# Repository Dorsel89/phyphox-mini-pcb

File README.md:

# phyphox:mini – PCB

KiCad project for the **phyphox:mini**, a small Bluetooth LE sensor board that
streams its measurements to the [phyphox](https://phyphox.org) app.

The design files were created with **KiCad 10**. Older KiCad versions cannot
open them.

## Hardware

| Part | Function |
|---|---|
| Nordic **nRF52832** (QFN48) | MCU with Bluetooth LE, internal DC/DC converter |
| ST **LSM6DSR** | accelerometer and gyroscope |
| Bosch **BMP580** | air pressure and temperature |
| TI **HDC1080** | relative humidity and temperature |
| Sensirion **STCC4** | CO₂ |
| Renesas/Adesto **AT25FF161A** | 16 Mbit (2 MB) SPI flash for data logging and firmware updates |
| 32 MHz and 32.768 kHz crystals | radio clock and low-power real-time clock |
| PCB antenna | 2.4 GHz, after TI application note SWRA117D |
| LED, test pads | status LED, programming and debugging (SWD) |

- 4-layer board, about 20 × 30 mm
- IMU and flash are connected via SPI; pressure, humidity and CO₂ sensors
  share one I²C bus.

## Files

| Path | Content |
|---|---|
| `Keyfob_2025_nrf52832.kicad_pro` | KiCad project |
| `Keyfob_2025_nrf52832.kicad_sch` | schematic |
| `Keyfob_2025_nrf52832.kicad_pcb` | board layout |
| `lib/` | project symbols (`*.kicad_sym`), footprints (`phyphox-footprints.pretty`) and 3D models (`3d/`) |

The project libraries are referenced relative to the project directory
(`sym-lib-table`, `fp-lib-table`), so the project opens without further setup.

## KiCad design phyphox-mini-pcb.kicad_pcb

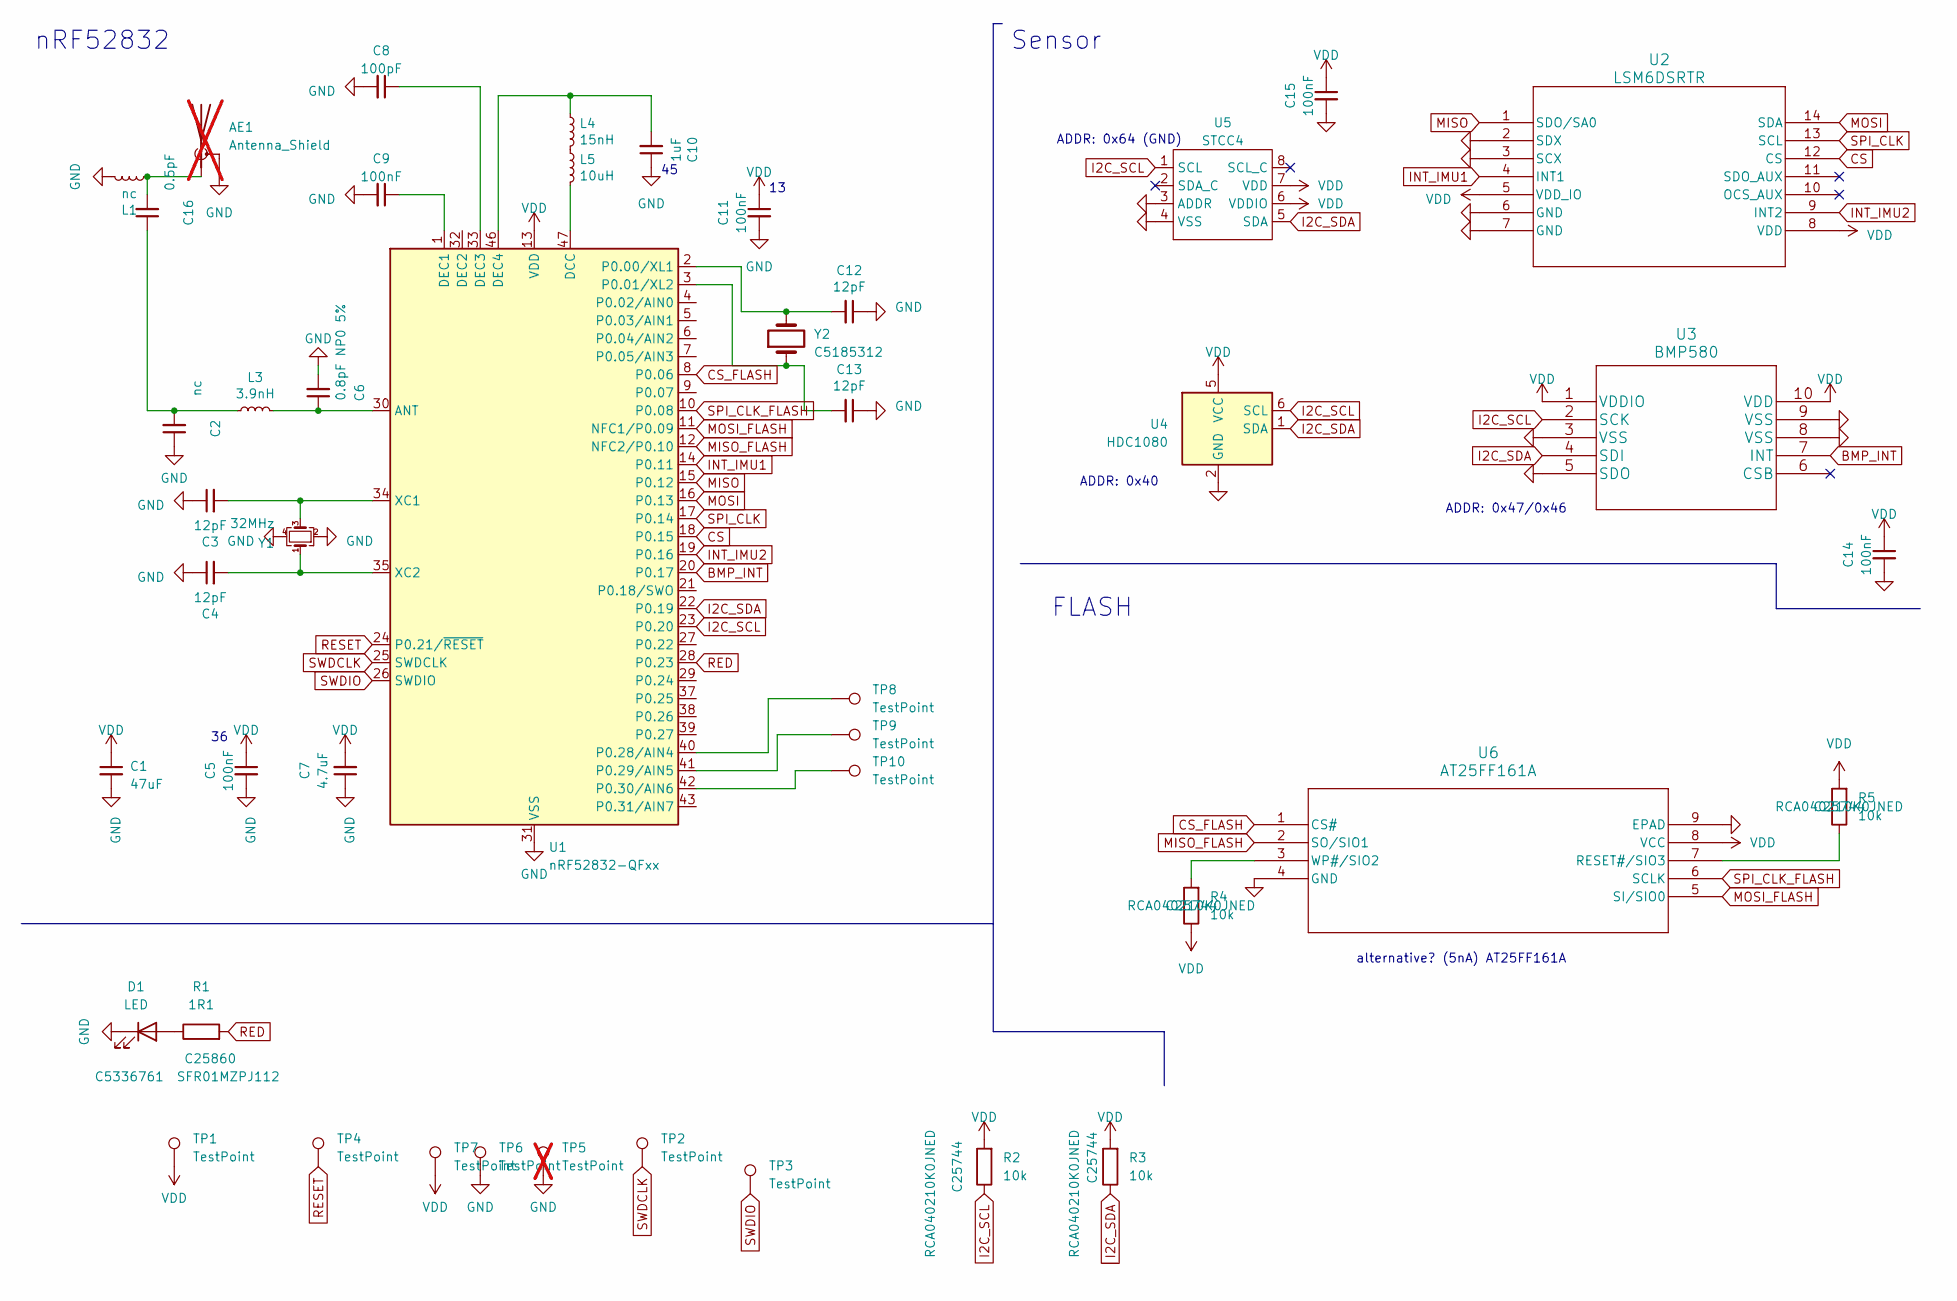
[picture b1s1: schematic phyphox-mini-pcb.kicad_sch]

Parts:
AE1: Antenna_Shield; Texas_SWRA117D_2.4GHz_Right; not fitted
C1: 47uF; C_0805_2012Metric; Manufacturer Part CL21A476MQYNNNE; LCSC Part C16780
C2: nc; C_0402_1005Metric
C3, C4, C12, C13: 12pF; C_0402_1005Metric; Manufacturer Part CC0402GRNPO9BN120; LCSC Part C526985
C5, C9, C11, C14, C15: 100nF; C_0402_1005Metric; Manufacturer Part CL05B104KA5NNNC; LCSC Part C307331
C6: 0.8pF NP0 5%; C_0402_1005Metric; LCSC Part C76915
C7: 4.7uF; C_0402_1005Metric; Manufacturer Part CL05A475KP5NRNC; LCSC Part C23733
C8: 100pF; C_0402_1005Metric; Manufacturer Part KGM05ACG1H101FN; LCSC Part C1546
C10: 1uF; C_0402_1005Metric; Manufacturer Part CL05A105KO5NNNC; LCSC Part C52923
C16: 0.5pF; C_0402_1005Metric; LCSC C76912
D1: LED; LED_0402_1005Metric; LCSC C5336761
L1: nc; L_0402_1005Metric
L3: 3.9nH; L_0402_1005Metric; Manufacturer Part MLG1005S3N9BT000; LCSC Part C14033
L4: 15nH; L_0402_1005Metric; Manufacturer Part MLG1005S15NJT000; LCSC Part C27143
L5: 10uH; L_0603_1608Metric; Manufacturer Part MLF1608E100KTD00; LCSC Part C1035
R1: 1R1; R_0402_1005Metric; Manufacturer Part SFR01MZPJ112; LCSC C25860
R2, R3, R4, R5: 10k; R_0402_1005Metric; Manufacturer Part RCA040210K0JNED; LCSC C25744
TP1: TestPoint; MY-ZJ-128; LCSC C5354946
TP2, TP3, TP4, TP6, TP7, TP8, TP9, TP10: TestPoint; TestPoint_Pad_D1.0mm
TP5: TestPoint; phyfob_bat_dot; not fitted
U1: nRF52832-QFxx; QFN-48-1EP_6x6mm_P0.4mm_EP4.6x4.6mm; LCSC Part C77540
U2: LSM6DSRTR; lsm6dsr; LCSC Part C784817
U3: BMP580; BMP581; LCSC Part C22391138
U4: HDC1080; Texas_PWSON-N6; LCSC Part C2864159
U5: STCC4; LCSC C49191471
U6: AT25FF161A; USON-8L-2X3X0P6_MAC; LCSC C152595
Y1: 32MHz; Crystal_SMD_2016-4Pin_2.0x1.6mm; Manufacturer Part X201632MKB4SI; LCSC Part C718072
Y2: C5185312; Crystal_SMD_3215-2Pin_3.2x1.5mm; LCSC Part C5185312

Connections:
BMP_INT: U1.20 (P0.17), U3.7 (INT)
CS: U1.18 (P0.15), U2.12 (CS)
CS_FLASH: U1.8 (P0.06), U6.1 (CS#)
GND: AE1.2 (Shield), C1.2, C2.1, C3.1, C4.1, C5.2, C6.2, C7.1, C8.2, C9.2, C10.1, C11.2, C12.1, C13.1, C14.2, C15.2, D1.1 (K), L1.2, TP5.1 (1_1), TP6.1 (1_1), U1.31 (VSS), U1.45 (VSS), U1.49 (VSS), U2.2 (SDX), U2.3 (SCX), U2.6 (GND), U2.7 (GND), U3.3 (VSS), U3.5 (SDO), U3.8 (VSS), U3.9 (VSS), U4.2 (GND), U5.3 (ADDR), U5.4 (VSS), U6.4 (GND), U6.9 (EPAD), Y1.2, Y1.4
I2C_SCL: R2.1, U1.23 (P0.20), U3.2 (SCK), U4.6 (SCL), U5.1 (SCL)
I2C_SDA: R3.1, U1.22 (P0.19), U3.4 (SDI), U4.1 (SDA), U5.5 (SDA)
INT_IMU1: U1.14 (P0.11), U2.4 (INT1)
INT_IMU2: U1.19 (P0.16), U2.9 (INT2)
MISO: U1.15 (P0.12), U2.1 (SDO/SA0)
MISO_FLASH: U1.12 (NFC2/P0.10), U6.2 (SO/SIO1)
MOSI: U1.16 (P0.13), U2.14 (SDA)
MOSI_FLASH: U1.11 (NFC1/P0.09), U6.5 (SI/SIO0)
unnamed: AE1.1 (A), C16.2, L1.1
unnamed: C2.2, C16.1, L3.1
unnamed: D1.2 (A), R1.1
unnamed: L4.2, L5.1
unnamed: C6.1, L3.2, U1.30 (ANT)
unnamed: L5.2, U1.47 (DCC)
unnamed: C9.1, U1.1 (DEC1)
unnamed: C8.1, U1.33 (DEC3)
unnamed: C10.2, L4.1, U1.46 (DEC4)
unnamed: C12.2, U1.2 (P0.00/XL1), Y2.2
unnamed: C13.2, U1.3 (P0.01/XL2), Y2.1
unnamed: TP8.1 (1_1), U1.40 (P0.28/AIN4)
unnamed: TP9.1 (1_1), U1.41 (P0.29/AIN5)
unnamed: TP10.1 (1_1), U1.42 (P0.30/AIN6)
unnamed: C3.2, U1.34 (XC1), Y1.3
unnamed: C4.2, U1.35 (XC2), Y1.1
unnamed: R5.1, U6.7 (RESET#/SIO3)
unnamed: R4.2, U6.3 (WP#/SIO2)
RED: R1.2, U1.28 (P0.23)
RESET: TP4.1 (1_1), U1.24 (P0.21/~RESET)
SPI_CLK: U1.17 (P0.14), U2.13 (SCL)
SPI_CLK_FLASH: U1.10 (P0.08), U6.6 (SCLK)
SWDCLK: TP2.1 (1_1), U1.25 (SWDCLK)
SWDIO: TP3.1 (1_1), U1.26 (SWDIO)
VDD: C1.1, C5.1, C7.2, C11.1, C14.1, C15.1, R2.2, R3.2, R4.1, R5.2, TP1.1 (1_1), TP7.1 (1_1), U1.13 (VDD), U1.36 (VDD), U1.48 (VDD), U2.5 (VDD_IO), U2.8 (VDD), U3.1 (VDDIO), U3.10 (VDD), U4.5 (VCC), U5.6 (VDDIO), U5.7 (VDD), U6.8 (VCC)

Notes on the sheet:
FLASH
ADDR: 0x47/0x46
ADDR: 0x64 (GND)
alternative? (5nA) AT25FF161A
Sensor
ADDR: 0x40
nRF52832

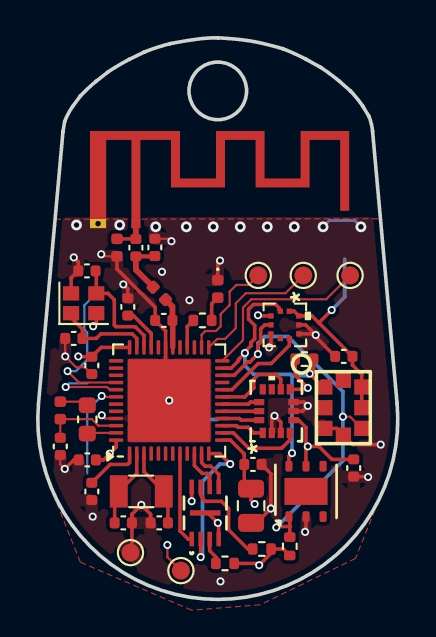
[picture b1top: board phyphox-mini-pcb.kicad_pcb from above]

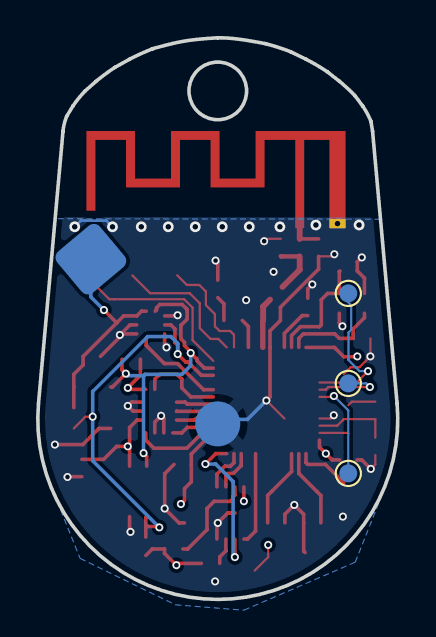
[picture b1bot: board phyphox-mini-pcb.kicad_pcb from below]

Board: 4 copper layers, 20.0 x 31.2 mm, 45 parts (5 on the bottom side), 37 nets.

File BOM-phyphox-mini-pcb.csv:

"Reference","Value","Footprint","Qty","DNP","Digikey","Hersteller-Teilenummer","JLC Part","Manufacturer Part"
"C1","47uF","Capacitor_SMD:C_0805_2012Metric","1","","","","C16780","CL21A476MQYNNNE"
"C2,L1","nc","Capacitor_SMD:C_0402_1005Metric,Inductor_SMD:L_0402_1005Metric","2","","","","",""
"C3,C4,C12,C13","12pF","Capacitor_SMD:C_0402_1005Metric","4","","","","C526985","CC0402GRNPO9BN120"
"C5,C9,C11,C14,C15","100nF","Capacitor_SMD:C_0402_1005Metric","5","","1276-6720-1-ND","","C1525","CL05B104KA5NNNC"
"C6","0.8pF NP0 5%","Capacitor_SMD:C_0402_1005Metric","1","","","","",""
"C7","4.7uF","Capacitor_SMD:C_0402_1005Metric","1","","1276-1784-1-ND","","C23733","CL05A475KP5NRNC"
"C8","100pF","Capacitor_SMD:C_0402_1005Metric","1","","478-1082-1-ND","","C1546"," KGM05ACG1H101FN "
"C10","1uF","Capacitor_SMD:C_0402_1005Metric","1","","1276-1067-1-ND","","C52923","CL05A105KO5NNNC"
"C16","0.5pF","Capacitor_SMD:C_0402_1005Metric","1","","","","",""
"D1","LED","LED_SMD:LED_0402_1005Metric","1","","","","",""
"L3","3.9nH","Inductor_SMD:L_0402_1005Metric","1","","","","C14033","MLG1005S3N9BT000"
"L4","15nH","Inductor_SMD:L_0402_1005Metric","1","","","","C27143","MLG1005S15NJT000"
"L5","10uH","Inductor_SMD:L_0603_1608Metric","1","","","","C1035","MLF1608E100KTD00"
"R1","1R1","Resistor_SMD:R_0402_1005Metric","1","","","",""," SFR01MZPJ112 "
"R2,R3,R4,R5","10k","Resistor_SMD:R_0402_1005Metric","4","","","",""," RCA040210K0JNED "
"TP1","TestPoint","phyphox-footprints:MY-ZJ-128","1","","","","",""
"TP5","TestPoint","phyphox-footprints:phyfob_bat_dot","1","Nicht bestücken","","","",""
"U1","nRF52832-QFxx","Package_DFN_QFN:QFN-48-1EP_6x6mm_P0.4mm_EP4.6x4.6mm","1","","","","",""
"U2","LSM6DSRTR","phyphox-footprints:lsm6dsr","1","","","","",""
"U3","BMP580","phyphox-footprints:BMP581","1","","","","",""
"U4","HDC1080","Package_SON:Texas_PWSON-N6","1","","","","",""
"U5","STCC4","phyphox-footprints:STCC4","1","","","","",""
"U6","AT25FF161A","phyphox-footprints:USON-8L-2X3X0P6_MAC","1","","","MX25R1635FZUIL0","",""
"Y1","32MHz","Crystal:Crystal_SMD_2016-4Pin_2.0x1.6mm","1","","","","C718072","X201632MKB4SI"
"Y2","C5185312","Crystal:Crystal_SMD_3215-2Pin_3.2x1.5mm","1","","","C5185312","",""
